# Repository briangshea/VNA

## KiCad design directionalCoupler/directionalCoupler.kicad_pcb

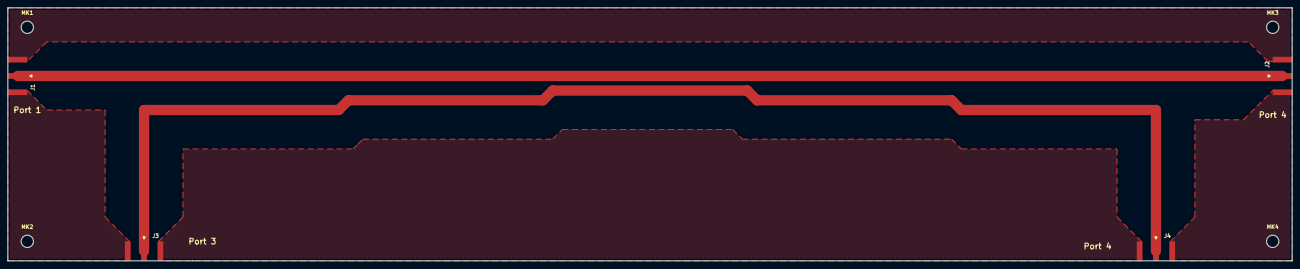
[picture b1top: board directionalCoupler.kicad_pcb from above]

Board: 2 copper layers, 335.3 x 66.0 mm, 8 parts (0 on the bottom side), 3 nets.

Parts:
J1, J2, J3, J4: SMA; SMA_Amphenol_132289_EdgeMount
MK1, MK2, MK3, MK4: Mounting_Hole_PAD; MountingHole_3.2mm_M3_DIN965

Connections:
GNDREF: J1.2, J2.2, J3.2, J4.2, MK1.1, MK2.1, MK3.1, MK4.1
unnamed: J1.1, J2.1
unnamed: J3.1, J4.1

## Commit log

2018-07-19 Initial Commit of kiCad drawings
2018-07-19 Fixed 4-Way resistive splitter in LO.sch (incomplete) Added BlockDiagram.pdf (incomplete) Changed Annoatated RF_to_IF.sch and set 0dB Attenuator to -6dBm
2018-07-19 Annoatated Schematics
